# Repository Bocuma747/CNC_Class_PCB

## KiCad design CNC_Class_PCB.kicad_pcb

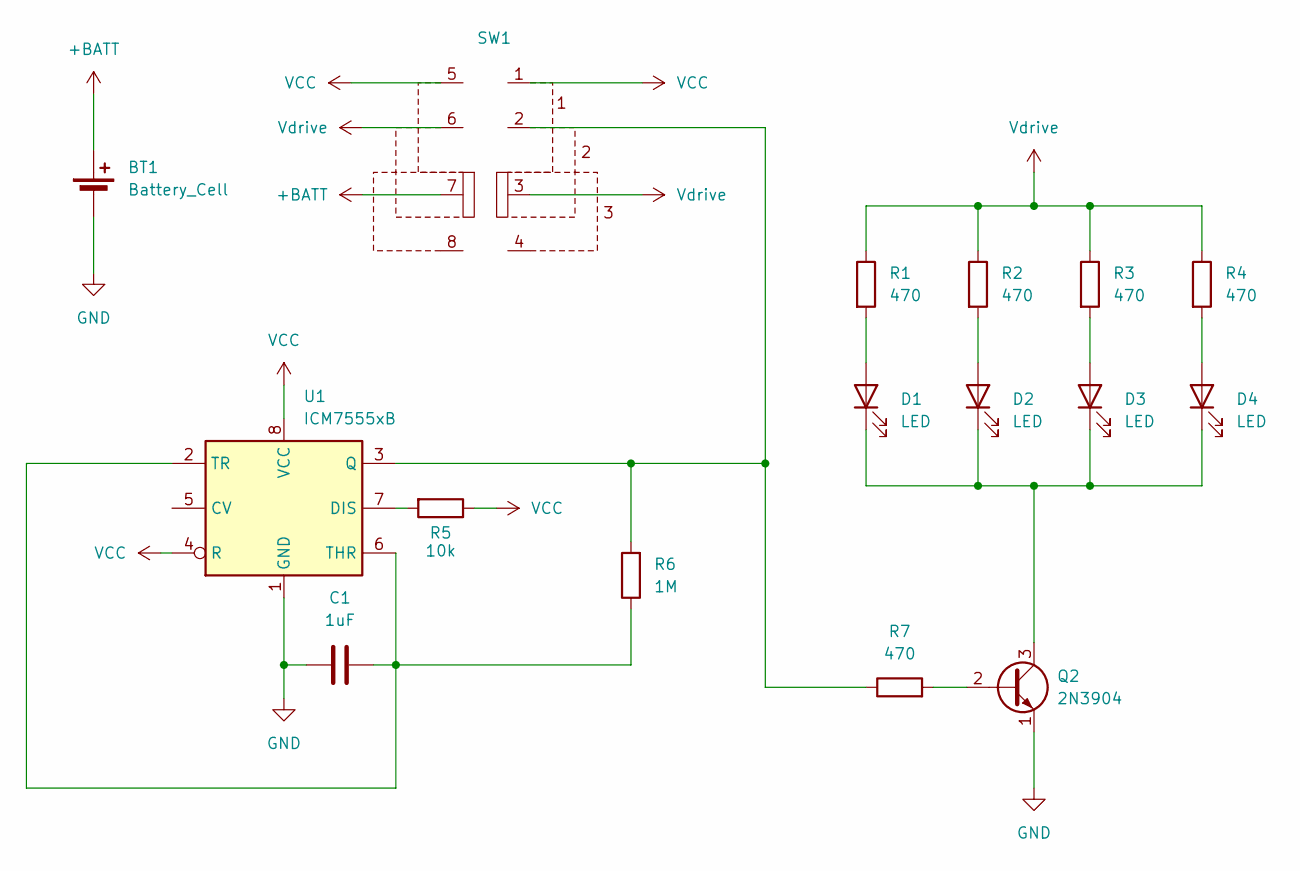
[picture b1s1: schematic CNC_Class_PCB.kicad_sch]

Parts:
BT1: Battery_Cell; BAT-HLD-003-SMT
C1: 1uF; C_1206_3216Metric_Pad1.33x1.80mm_HandSolder
D1, D2, D3, D4: LED; LED_1206_3216Metric_Pad1.42x1.75mm_HandSolder
Q2: 2N3904; TO-92_Inline
R1, R2, R3, R4: 470; R_Axial_DIN0207_L6.3mm_D2.5mm_P10.16mm_Horizontal
R5: 10k; R_1206_3216Metric_Pad1.30x1.75mm_HandSolder
R6: 1M; R_1206_3216Metric_Pad1.30x1.75mm_HandSolder
R7: 470; R_1206_3216Metric_Pad1.30x1.75mm_HandSolder
SW1: SLW-133538-2A-SMT-TR
U1: ICM7555xB; SOIC-8_3.9x4.9mm_P1.27mm

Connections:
+BATT: BT1.1 (+), SW1.7
GND: BT1.2 (-), C1.1, Q2.1 (E), U1.1 (GND)
unnamed: D1.2 (A), R1.2
unnamed: D1.1 (K), D2.1 (K), D3.1 (K), D4.1 (K), Q2.3 (C)
unnamed: D2.2 (A), R2.2
unnamed: D3.2 (A), R3.2
unnamed: D4.2 (A), R4.2
unnamed: Q2.2 (B), R7.2
unnamed: R5.2, U1.7 (DIS)
unnamed: R6.2, R7.1, SW1.2, U1.3 (Q)
unnamed: C1.2, R6.1, U1.2 (TR), U1.6 (THR)
VCC: R5.1, SW1.1, SW1.5, U1.4 (R), U1.8 (VCC)
Vdrive: R1.1, R2.1, R3.1, R4.1, SW1.3, SW1.6

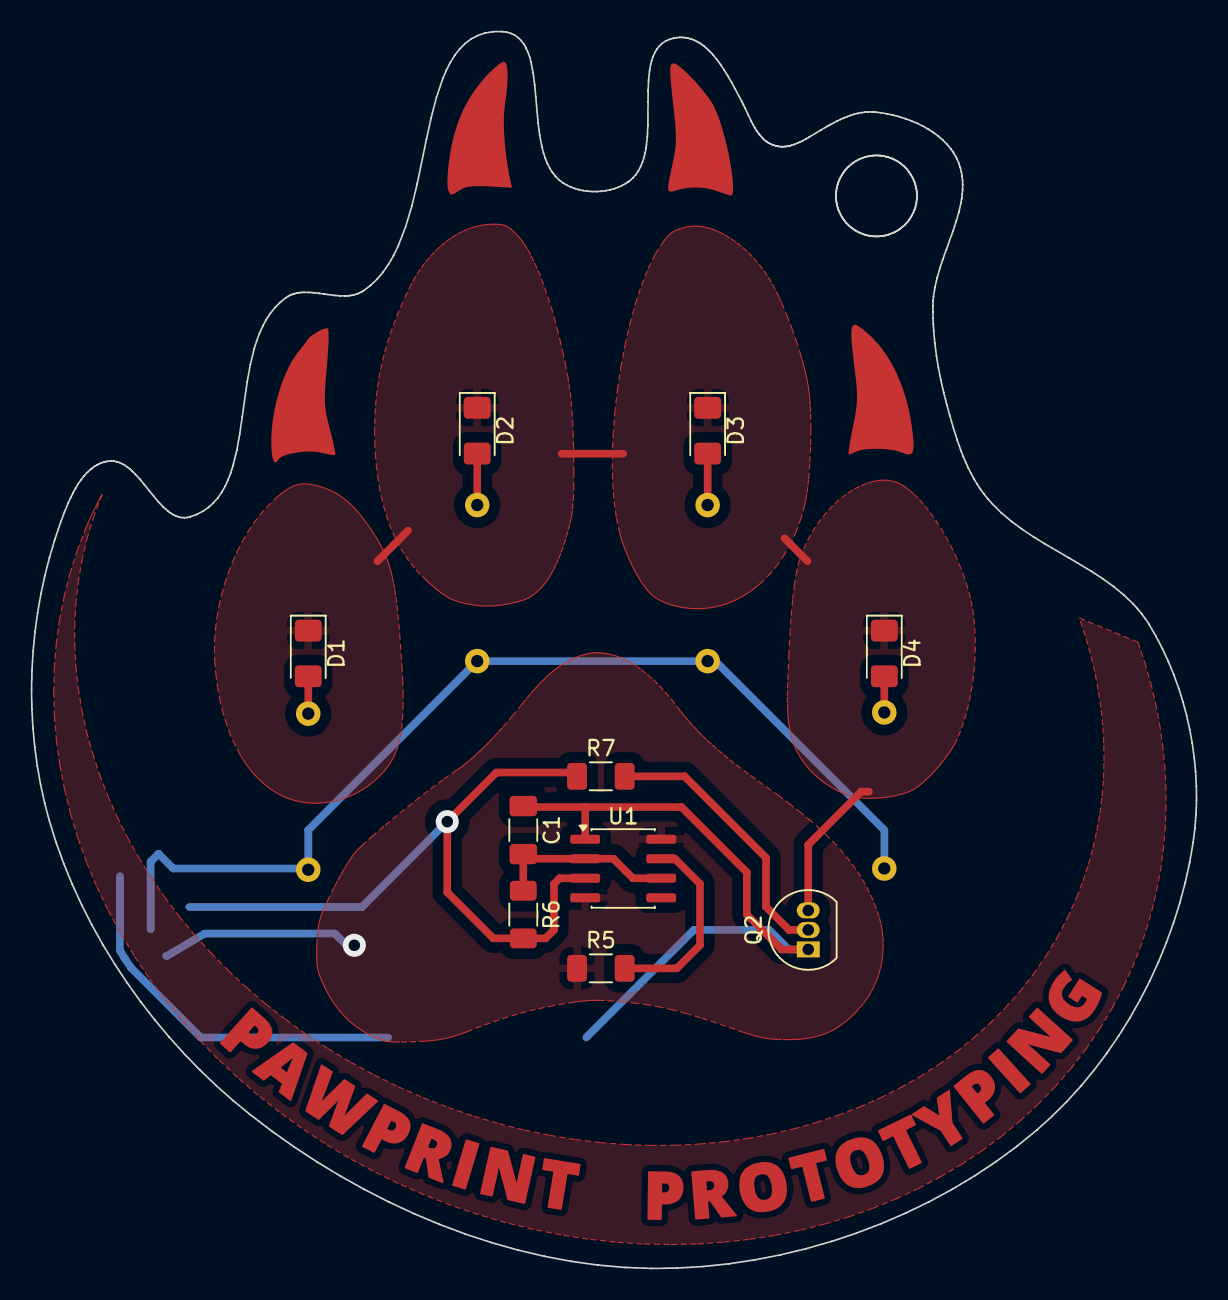
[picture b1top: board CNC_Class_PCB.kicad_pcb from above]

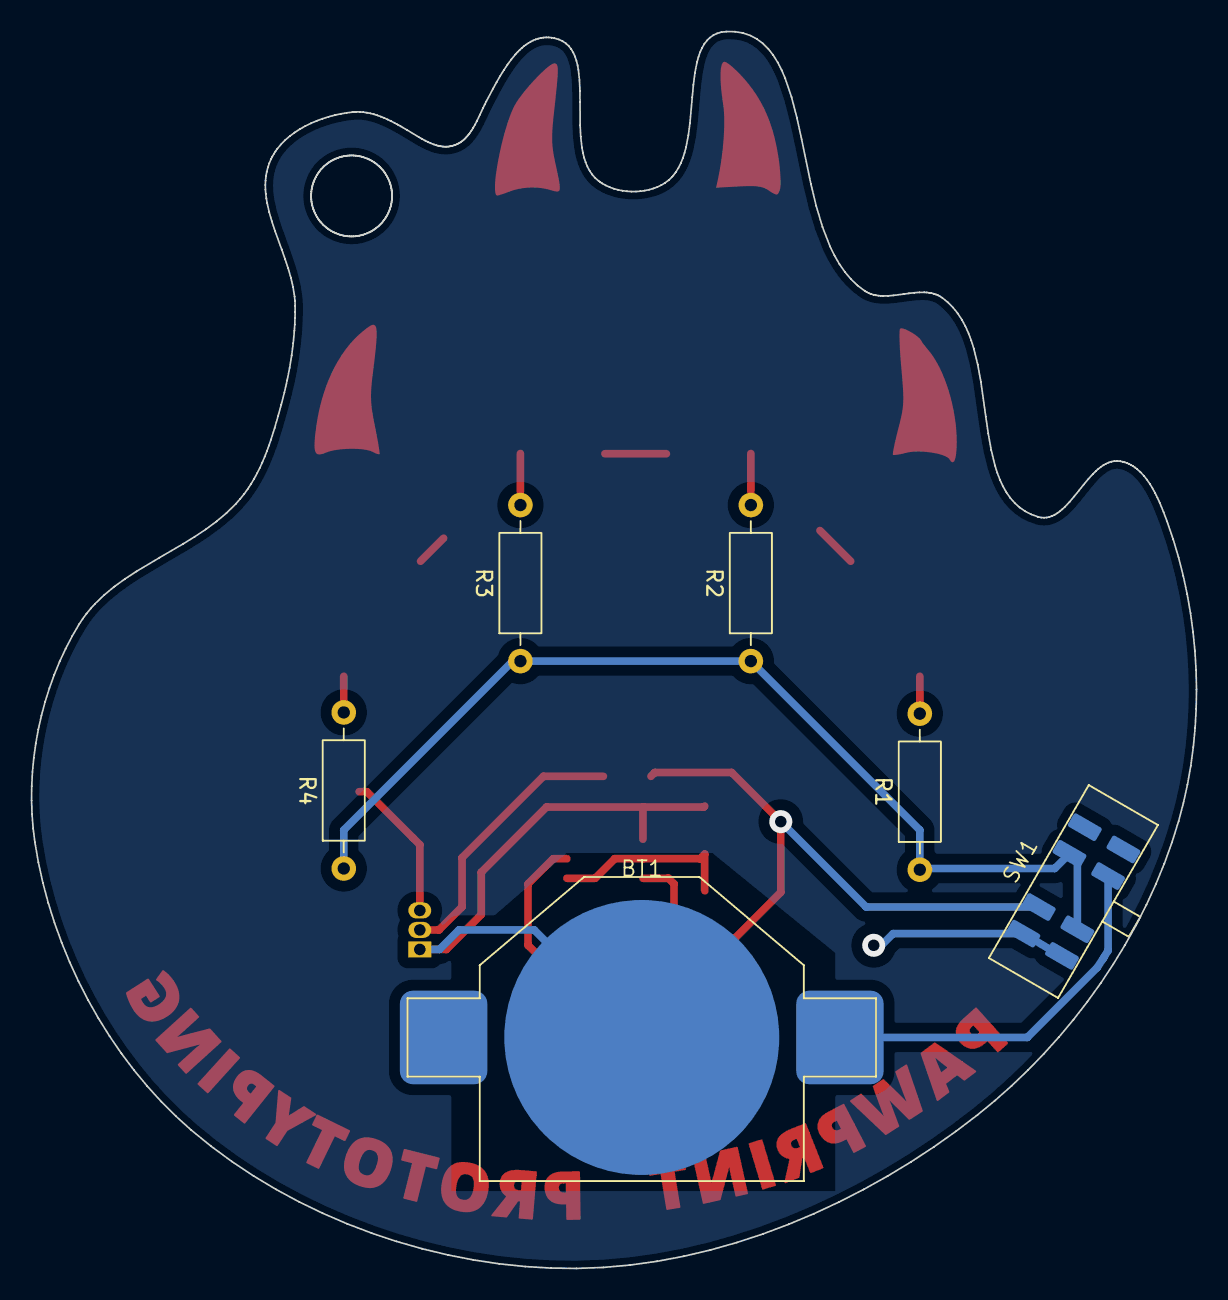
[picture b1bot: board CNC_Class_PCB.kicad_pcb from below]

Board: 2 copper layers, 75.8 x 80.5 mm, 16 parts (6 on the bottom side), 13 nets.

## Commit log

2025-12-02 smol
